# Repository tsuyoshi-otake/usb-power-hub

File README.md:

# USB Power-Control Hub

A 2-channel switched USB-C hub that measures each downstream port's current from
0.1 µA to 1 A, so a device under test can be power-profiled and power-cycled from
the host PC over a plain COM port.

*A rendered picture of the design files, not a photograph: nothing is printed or assembled
yet. [What it looks like](#what-it-looks-like) explains each face.*

> **Status (2026-11-21): the main board is ordered and in production. Nothing is built or
> measured, and there is no firmware.**
>
> - **Main board, Rev0.7 r01: `ORDERED`.** The user ordered it from JLCPCB and paid for it on
>   2026-11-20 (5 boards, 2 of them assembled) and had the production file confirmed on
>   2026-11-21. Its files are `manufacturing/releases/rev0.7/r01/` and are never overwritten.
>   It went out with gates open: JLCDFM never ran on Rev0.7, the stackup was not named on the
>   order, and the open issues of `CLAUDE.md` Section 11 stand (`RELEASE_MANIFEST.md` there,
>   *Open gates*). Its solder mask is green: JLCPCB takes only green on an Economic 4-layer
>   order.
> - **Enclosure, Rev0.5: drawn, not printed.** A printed tray, frame and cover with a PCB lid
>   let into the frame (`design/mechanical/`). No cable has been tried in an opening.
> - **Lid PCB, Rev0.2: drawn, not ordered.** JLCPCB has not seen its files.
> - **Firmware: does not exist.** The PC software (`host/profiler/`) runs against its demo
>   device.
> - **Every other release** (`manufacturing/releases/rev0.4/` to `rev0.6/`) stays `WIP` and
>   is not orderable. No further order is placed without the user's approval.

## What it is meant to do

- **Two USB-C inputs:**
  - `HOST` (J1) carries data and logic power from the PC.
  - `5V IN` (J4) is a power-only 5 V input that feeds the ports. Its USB-C current
    advertisement is read and enforced.
  - There is no USB-PD and no port regulator: the port voltage is J4's minus up to 0.40 V
    at 1 A (0.48 V when the other port also draws 1 A; the input fuse is shared).
- **Downstream:** two USB-C receptacles (`OUT A`, `OUT B`), each switched on and off
  independently by firmware. They are OFF at power-up and after any reset (REQ-PORT-01),
  and offer Default USB power (500 mA), with a hardware over-current trip at 1.16 A. Each
  port's D+ and D− are also tapped through 1 kΩ to four RP2040 GPIO for a Low-Speed and
  Full-Speed capture of the device under test (D38, issue #10); firmware for it does not exist.
- **Measurement:** per port, a 3-range shunt ladder (510 Ω / 10 Ω / 0.1 Ω) with hardware
  up-ranging, discrete current-mirror amplifiers, and two 12-bit MCP3208 ADCs (one per
  port, sampled together), at 14.0 kSPS per channel. Accuracy target: ±(1 % + 3 LSB of the range).
- **Control:** an RP2040 with its own flash and crystal, machine-placed (D29), behind a CH335F hub, also machine-placed (D31), enumerating as a driverless CDC-ACM COM
  port. Commands such as `PORT A ON`, `PORT B CYCLE 2000` and `STREAM ON` are listed in
  `requirements/product.md` Section 4.1.
- **Board:** 100 × 72 mm, 4 layers, 1.6 mm FR-4 (D24), leaded HASL (D30). The earlier 85 × 35 mm
  cannot hold the Rev0.4 parts. JLCPCB's instant quote on 2026-11-03 (4 layers, 5 pcs,
  default options, leaded HASL) was $8.00 at 85 × 35, 100 × 72 and 100 × 100 mm; ENIG would
  add $16.90 and $17.40 at the two sizes. Recheck the live quote before ordering. The stackup is
  JLC04161H-7628, named on the order, without impedance control for the prototype (D27).
  - JLCPCB machine-places the small parts, the RP2040, the CH335F and the four USB-C
    receptacles, all JLCPCB **Basic** except those three parts (Extended, the user's three
    exceptions, D29, D31 and D37).
  - You hand-solder the large parts, all bought from **Akizuki**: two DIP16 ADCs, the 12 V
    module, two shunts per port and the input fuse.
  - This is the sourcing rule D13. D22 excludes Preferred Extended parts too, so the
    D+/D− lines of J1–J3 have no ESD protection (`requirements/product.md` §9).

## What it looks like

The unit is 104.8 × 76.8 × 27.7 mm, everything matte black (Enclosure E2, Lid K7). The
pictures are rendered from the generated design files: the enclosure's STL files and the lid's
KiCad board. They are not photographs and they prove nothing. Nothing is printed, the lid PCB
is not ordered, and the screws, the receptacles and the lit LEDs are drawn by the render
script.

| Front | Back |
|---|---|
|  |  |
| `OUT A` (left) and `OUT B` (right), the two switched and measured ports, 65 mm apart. Each opening has a 15.0 × 8.0 mm pocket for the plug's overmould (E6). The line along the wall is the seam between the tray below and the frame above. | `HOST` (data and logic power from the PC) and `5V IN` (the power-only input that feeds the ports). The flat piece between them is the printed cover (E11) of the opening for the SWD spring-pin clamp (J5, D40): it is drawn out with a fingernail before the clamp goes on. |

The top is a PCB, not a printed part (Lid Rev0.2: bare 2-layer, 1.6 mm, matte black mask,
white legend, no component and no net).

1. **It lies inside the case.** The frame's wall goes on up round the lid, as high as the
   lid is thick, so the lid's edge is not seen and its top face is flush with the wall's
   (E12; 0.4 mm between lid and wall).
2. **Four M2 screws** hold it on the frame's posts; four more from below clamp the main board
   between tray and frame (E4, heat-set inserts).
3. **A label and an arrow for each port:** `HOST`, `5V IN`, `OUT A`, `OUT B`.
4. **A button and a window beside each output.** The button is a loose printed plunger over
   the port's switch on the main board. The window is bare FR-4, with no copper and no mask,
   over the port's two LEDs (green: port on, red: port fault), so no light pipe is needed (E8).
5. **`BOOT` is a pinhole** for a paperclip to SW3, which starts the RP2040's USB bootloader
   without opening the case (REQ-BOOT-02).

What is not known before a print (the lid's fit in its pocket, how the support under the
lid's seat comes off, the cover's click, a real cable in an opening) is listed in
`design/mechanical/ENCLOSURE_Rev0.5.md` §10. To draw the pictures again, with Blender 5.x and
KiCad 9.0 (about 1 min on a GPU):

```sh
"<Blender>/blender.exe" -b --python design/mechanical/scripts/render_unit.py -- --kicad-cli "<KiCad 9.0>/bin/kicad-cli.exe"
```

## Documents

Read in this order:

| File | What it holds |
|---|---|
| `CLAUDE.md` | Engineering policy, release discipline, and the open-issue list (Section 11). Every unstruck open issue blocks manufacturing. |
| `requirements/product.md` | What the product must do — the authority. REQ-* IDs, each marked Settled / Delegated / Proposed / Open / Withdrawn. Includes the control protocol. |
| `requirements/verification.md` | How each requirement is proven (V-* IDs: method, pass criterion, limits). |
| `design/circuit/CIRCUIT_DESIGN_Rev0.7.md` | The schematic as a document: topology, nets, designators, calculations, decisions (§10), and what was given up to meet the sourcing rule (§7.4). Rev0.1–Rev0.4 are in Git history (Rev0.4 at commit `5a697aa`). |
| `requirements/parts.md` | Candidate parts: JLCPCB Basic rows (LCSC number, assembly stock, class, date) and Akizuki rows (code, stock, price, date). Candidates only — none is confirmed. |
| `design/ecad/` | The KiCad 9 project (D32): `source/` holds the project, the source of truth until the EasyEDA import; `scripts/` holds its generators and checks; `libraries/` holds the project's symbols and footprints and the parts register they are checked against (its README). So far: stackup, outline, rules, net classes, the libraries, the schematic, written from `design/circuit/CIRCUIT_DESIGN_Rev0.7_netlist.md` (the capture list: every part, pin and net) and checked against it, the placement and silkscreen, written from `design/ecad/PLACEMENT_Rev0.7.md` (where every part and label sits, and why), and the routing, from `design/ecad/ROUTING_Rev0.7.md`; `make_outputs.py` writes the candidate manufacturing set from the board. `design/ecad/README.md` gives the order to run the generators in. |
| `design/experiments/oi-23-placement/` | The OI-23 placement study: why 85 × 35 mm cannot work, and the checked 100 × 72 mm block placement. A trial, not design data. |
| `design/experiments/stackup-impedance/` | The stackup study behind D27: JLCPCB's 4-layer stackups, the 90 Ω USB pair width on each, and a model checked against JLCPCB's single-ended calculator. A non-authoritative study, not design data. |
| `design/experiments/cost-estimate/` | Prototype cost estimate, dated 2026-11-03, re-run 2026-11-04 for D29, D30, D31 and D33, with Rev0.4's real quote (2026-11-12), the Rev0.5 delta for D37 and D38 and Rev0.5's quote (2026-11-13): 5 bare PCBs with 2 assembled by JLCPCB, plus the Akizuki parts. An estimate, not a quote. |
| `design/experiments/usb-symmetry-c2/` | Trial C2 (issue #12): the four USB-C receptacles and the two buttons mirrored about the board's centre line, at placement level and, without a patch, at routing level. The parts fit and `check_pcb.py` passes on a footprint-only board; one router run left 15 connections open, against 16 on the board at the same stage. A trial, not design data. D39 then took its placement into the board as Rev0.6 (issue #13); the board's routing is its own (`design/ecad/ROUTING_Rev0.7.md`), not the trial's. |
| `design/mechanical/` | The enclosure (issue #11; Rev0.5 for the Rev0.7 board, issue #14), a first design on paper: `ENCLOSURE_Rev0.5.md` (a printed tray and frame with a PCB lid let into the frame, 104.8 × 76.8 × 27.7 mm; its decisions E1–E12, the opening for the SWD clamp, its printed cover and the wall round the lid among them, and what is not verified), the board's mechanical interface exported from the KiCad board, the STL files, eleven pictures of the build, four realistic renders of the assembled unit (`render_unit.py`, for looking at), and the scripts that generate and check them (its README). Nothing is printed and no cable has been tried. The lid PCB is drawn as its own KiCad board (`LID_Rev0.2.md`, `lid/`: bare 2-layer, the main board's outline, the legend on its top); it is not ordered. |
| `host/profiler/` | The PC software (issue #9): a native Win32 current profiler in Rust that plots both channels, switches the ports and exports CSV. Runs against its demo device until firmware exists (its README). |
| `mockup/` | three.js appearance model of an earlier 60 × 24 mm, 6-layer concept. Reference only; superseded by the board-size decisions D10 and D24 (100 × 72 mm). |

Decisions are D-numbers in the circuit document's §10. Its "By" column says whether the
user made each one, whether it came from the Rev0.1 design, or whether Claude made it
under the user's 2026-11-03 delegation ("Claude (delegated)"). The user may revert a
delegated decision. Rev0.2's proposals (P-numbers) are resolved in §14.

## Re-checking part stock

Stock in `requirements/parts.md` is a dated snapshot. To re-query the JLCPCB
assembly-parts pool (Python 3, standard library only, no install step; checked with 3.13):

```sh
python tools/jlc_stock.py C7433 OP07CDR
python tools/jlc_stock.py --all OP07      # list every hit, for finding candidates
```

The full command for every listed part is at the top of `requirements/parts.md`.
Exit status: 0 = every query matched exactly, 1 = some query did not, 2 = the API
failed. The tool's docstring lists what it cannot see — electrical suitability,
order-time stock, footprints, price, and lifecycle. Akizuki stock has no tool: read the
product page (codes in `requirements/parts.md`) at order time.

## Viewing the mockup

The mockup loads three.js from unpkg, so it needs a network connection and an
HTTP server (ES modules do not load from `file://`):

```sh
python -m http.server 8000 --directory mockup
# then open http://localhost:8000/usb-power-hub-board.html
```

## Building and programming

Not possible yet: the first boards are in production at JLCPCB (Rev0.7 r01, ordered on
2026-11-20; `manufacturing/releases/rev0.7/r01/`, state `ORDERED`), and firmware does not
exist. What follows is how the design came to that order; the gates it names are Rev0.5's and
Rev0.6's. The board is captured and laid out in KiCad 9.0.8 until the design is
complete, then imported into EasyEDA (decision D32, issue #6). Every part has a symbol and
a footprint, the RP2040's, the CH335F's and the USB-C receptacle's lands drawn from their
datasheets or maker's drawing (G20, G21, D37). The schematic is captured (issue #6 P2,
D34) and includes J1's soft start (D35, issue #7) and the four data-line taps (D38, issue
#10). The parts are placed (P3) and routed (P4, under D36's L3/L4 rule): DRC reports 0
violations and 0 unconnected items, and `check_routing.py` rule 9 keeps the L2 plane whole
under U1 and U6. Rev0.6 moved 31 parts with the connectors (D39) and carries Rev0.5's routing
where it still stands (`design/ecad/scripts/carry.py`); the rest is a new router session and
a new patch. Rev0.7 changes J5's land (D40) and carries Rev0.6's routing the same way, with the
tracks at J5 drawn in the routing document. The silkscreen labels are placed, and a candidate manufacturing set (P5:
Gerber, drill, JLCPCB BOM and CPL, schematic PDF, renders, a `WIP` manifest) is generated
into `manufacturing/working/rev0.7/`, which Git does not track and nobody may order from;
`manufacturing/releases/rev0.5/r02/` holds Rev0.5's files as a release candidate (state
`WIP`, nothing ordered; r01 beside it is superseded). The JLCPCB gate ran on 2026-11-13
(JLCDFM, part mapping, the placement preview of the receptacle, a quote of $51.94 without
shipping; `JLCPCB_REVIEW.md`) and found two defects in r01, both fixed in r02: the receptacle's
JLCPCB model sat 1.375 mm off the CPL point, and eight vias stood 0.046 mm from its plated
slots. The decisions it leaves are the user's (the 0.60 mm slot width, impedance control,
shipping, approval); then comes the EasyEDA import (P6). The front-end checks are made on the first assembled board, not on a
bench beforehand (decision D28). Firmware does not exist.

The KiCad project, its libraries, its schematic and its board are generated, not hand-edited. With KiCad
9.0's own Python, from the repository root:

```sh
"<KiCad 9.0>/bin/python.exe" -I -B design/ecad/scripts/make_project.py           # writes and checks design/ecad/source
"<KiCad 9.0>/bin/python.exe" -I -B design/ecad/scripts/test_make_project.py      # the check's negative tests
"<KiCad 9.0>/bin/python.exe" -I -B design/ecad/scripts/make_libraries.py         # writes and checks design/ecad/libraries
"<KiCad 9.0>/bin/python.exe" -I -B design/ecad/scripts/test_check_libraries.py   # its negative tests
"<KiCad 9.0>/bin/python.exe" -I -B design/ecad/scripts/make_schematic.py         # writes the schematic, runs ERC and check_schematic.py
"<KiCad 9.0>/bin/python.exe" -I -B design/ecad/scripts/test_check_schematic.py   # its negative tests
"<KiCad 9.0>/bin/python.exe" -I -B design/ecad/scripts/autoroute.py --java <java.exe> --jar <freerouting-2.5.0.jar>  # only when its input changed
"<KiCad 9.0>/bin/python.exe" -I -B design/ecad/scripts/make_pcb.py               # places, routes and labels; runs check_pcb.py, check_routing.py, check_silk.py
"<KiCad 9.0>/bin/python.exe" -I -B design/ecad/scripts/test_check_pcb.py         # its negative tests
"<KiCad 9.0>/bin/python.exe" -I -B design/ecad/scripts/test_check_routing.py
"<KiCad 9.0>/bin/python.exe" -I -B design/ecad/scripts/test_check_silk.py
"<KiCad 9.0>/bin/python.exe" -I -B design/ecad/scripts/make_outputs.py           # writes manufacturing/working/rev0.7, runs check_outputs.py
"<KiCad 9.0>/bin/python.exe" -I -B design/ecad/scripts/test_check_outputs.py     # its negative tests
```

`make_project.py` writes a bare board, so `make_pcb.py` runs after it. `autoroute.py` needs
Freerouting 2.5.0 and a Java runtime, which are not in the repository
(`design/ecad/README.md`). A release candidate is also read against the board by two scripts that
share nothing with the generators, `independent_check_sets.py` and
`independent_check_positions.py` (`design/ecad/README.md`, *Independent check of a candidate set*).

## Repository

- Git since 2026-11-03. Commit `4dd10fb` is the design exactly as it was paused
  on 2026-08-16; later commits are the 2026-11-03 revision.
- **Remote:** `origin` is the GitHub repository `tsuyoshi-otake/usb-power-hub`, private from
  2026-11-03 and public since 2026-11-20 by the user's decision, under the MIT licence
  (`LICENSE`). No account data, credential or address goes into it (`CLAUDE.md` Section 2).
- Commit messages are English and describe the change in detail.

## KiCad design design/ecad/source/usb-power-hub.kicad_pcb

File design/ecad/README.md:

# KiCad project (Rev0.7, issues #6, #8, #10, #13, #14)

> **WIP — MANUFACTURING PROHIBITED.** Rev0.7 is captured, placed, routed and labelled in
> KiCad 9.0.8 until the design is complete, then imported into EasyEDA (D32). Its candidate
> manufacturing set (step 7) is a `WIP` set: nothing here is orderable.

Everything under `source/` and `libraries/` is generated by the scripts in `scripts/` from
documents in the repository. Change the document, then re-run the generator. A board or
schematic saved from the KiCad GUI is overwritten by the next run; open the project to look,
not to edit.

| Path | Holds |
|---|---|
| `source/` | The KiCad project: `usb-power-hub.kicad_pro` (rules, net classes), `usb-power-hub.kicad_dru` (JLCPCB's hole figures for vias and PTH pads as custom DRC rules, issue #8), the root sheet and six sub-sheets, `usb-power-hub.kicad_pcb` (stackup, outline, placed footprints). |
| `libraries/` | The project symbols and footprints and `library.json`, the datasheet facts they are checked against (its README). |
| `PLACEMENT_Rev0.7.md` | Where every part sits on the board, and why (P3), and its silkscreen labels: text, position, size, stroke and leader (P5). |
| `ROUTING_Rev0.7.md` | The plane, the hand-drawn tracks (USB pairs, Kelvin taps, power trunks), the zones, the router's classes, keepouts, layer preferences and costs, the patch drawn after the router, and why (P4). |
| `routing/` | `carried.json`, the tracks and vias of Rev0.5's routing that still stand on this board (written by `carry.py`); the router's session `usb-power-hub.ses` and `autoroute.json`, which records the router input, the jar, the Java runtime and the arguments that produced it. |
| `scripts/` | The generators, their checkers and the checkers' negative tests; the two independent checks of a candidate set. |

## Pipeline

Run with KiCad 9.0's own Python, which carries `pcbnew`, from the repository root, in this
order. Each generator runs its checker when it has written its files; exit status 0 means
written and checked.

| Step | Script | Reads | Writes | Checked by | Negative tests |
|---|---|---|---|---|---|
| 1 | `make_project.py` | `design/experiments/stackup-impedance/stackups.json` | `.kicad_pro`, `.kicad_dru`, a bare `.kicad_pcb` | `make_project.py --check` | `test_make_project.py` |
| 2 | `make_libraries.py` | `libraries/library.json` | `libraries/usb-power-hub.kicad_sym`, `usb-power-hub.pretty/` | `check_libraries.py` | `test_check_libraries.py` |
| 3 | `make_schematic.py` | `design/circuit/CIRCUIT_DESIGN_Rev0.7_netlist.md` (the capture list), the symbols | the seven `.kicad_sch` | ERC, `check_schematic.py` | `test_check_schematic.py` |
| 4 | `carry.py` | the step-6 inputs up to the GND fanout; the previous revision's carried record, session and patch table (Rev0.6's), read from Git history at the commit the carry table of `ROUTING_Rev0.7.md` names | `routing/carried.json` | `carry.py --check`; `make_pcb.py`, which refuses a record made for another board or from other sources | `test_carry.py` |
| 5 | `autoroute.py` | what `make_pcb.py --dsn` writes from the step-6 inputs, the carried record included | `routing/usb-power-hub.ses`, `routing/autoroute.json` | `make_pcb.py`, which refuses a session made from other input | — |
| 6 | `make_pcb.py` | the schematic's exported netlist, `PLACEMENT_Rev0.7.md`, `ROUTING_Rev0.7.md`, the carried record, the session, the footprints | `.kicad_pcb` | `make_project.py --check`, `check_pcb.py`, `check_routing.py` (each with DRC), `check_silk.py` | `test_check_pcb.py`, `test_check_routing.py`, `test_check_silk.py` |
| 7 | `make_outputs.py` | the project in `source/`, `design/ecad/jlcpcb_model_frame.json` | `manufacturing/working/rev0.7/`: Gerber and drill zip, JLCPCB BOM and CPL, hand-solder list, schematic and assembly PDFs, two renders, ERC and DRC reports, `RELEASE_MANIFEST.md` (state `WIP`), `SHA256SUMS.txt` | `check_outputs.py` | `test_check_outputs.py` |

```sh
"<KiCad 9.0>/bin/python.exe" -I -B design/ecad/scripts/make_project.py
"<KiCad 9.0>/bin/python.exe" -I -B design/ecad/scripts/make_libraries.py
"<KiCad 9.0>/bin/python.exe" -I -B design/ecad/scripts/make_schematic.py
"<KiCad 9.0>/bin/python.exe" -I -B design/ecad/scripts/carry.py
"<KiCad 9.0>/bin/python.exe" -I -B design/ecad/scripts/autoroute.py --java <java.exe> --jar <freerouting-2.5.0.jar> --passes 8
"<KiCad 9.0>/bin/python.exe" -I -B design/ecad/scripts/make_pcb.py
"<KiCad 9.0>/bin/python.exe" -I -B design/ecad/scripts/make_outputs.py
```

Step 4 needs the repository's Git history: it reads Rev0.6's carried record, session and patch table at the
commit the carry table names, and takes about 8 s on this machine. It is needed only when its
inputs change: `make_pcb.py` stops and asks for it when the record no longer matches the carry
table or the board before the carry.

Step 5 needs Freerouting 2.5.0 and a Java runtime, which are not in the repository; the
script refuses any jar or runtime other than the pinned ones (their SHA-256 is in the
script). It is needed only when its input changes: `make_pcb.py` stops and asks for it when
the session no longer matches the board it would route. The committed session took about
5 min on this machine (8 passes, single-threaded; `ROUTING_Rev0.7.md`, *Router*, says why more
passes change nothing while the carried copper is fixed). A new record or a new session also
needs a new patch table (`ROUTING_Rev0.7.md`, *After the router*).

`make_project.py` writes a bare board, so `make_pcb.py` runs after it; until then
`check_pcb.py` fails, because the board holds no footprints. A re-run of any generator but
`make_pcb.py` writes the same bytes: UUIDs are derived, and `make_pcb.py` seeds pcbnew's UUID
generator, which decides the order footprints are saved in.

`make_pcb.py` writes the same bytes except for the pours' fill: KiCad's zone filler is not
deterministic. Measured on the Rev0.5 board (commit `866ef44`): in 32 runs on 2026-11-13 (a
scratch copy of `design/`, `--no-check`), 3 left out two 0.11 mm² islands of the B.Cu GND pour
that touched pad J3.S1 where it then stood (x 96.73-97.23 and 105.37-105.87, y 117.0-117.3 mm)
and 29 kept them; the board file then differed by those two filled polygons and the Gerber's
`B_Cu` member with it. Nothing else differed, and both boards passed every check. The Rev0.6 board
has not been run that way. The tracked `source/usb-power-hub.kicad_pcb` is therefore the source of
truth, and a release is made from it. Do not regenerate it to compare, and read a changed board
hash after a re-run as this, not as a changed design, before looking for another cause. Step 7 is
deterministic given the board.

Step 7 writes a candidate, not a release. `manufacturing/working/` is not tracked
(`.gitignore`; CLAUDE.md §2: disposable, never orderable), so the set is regenerated rather
than checked out: the same sources, the board included, give the same bytes, because creation
dates are fixed to 1980-01-01 and paths made relative. Its manifest records the SHA-256 of every source file
instead of a Git commit, and `check_outputs.py` fails a set older than its sources. A
release is copied to `manufacturing/releases/<rev>/<rNN>/` and tracked there (CLAUDE.md §2).

The CPL's angles are KiCad's plus a per-LCSC rotation, and its positions KiCad's plus a per-LCSC
shift; both are in `jlcpcb_model_frame.json` (until 2026-11-13 `jlcpcb_model_rotation.json`,
rotations only), because JLCPCB applies a CPL point and angle to its own model of the part
(easy-stick 14.18). `make_outputs.py` reads it and `check_outputs.py` fails an entry no BOM line
uses. Gerber and drill files are written with the auxiliary origin at the board's lower-left
corner, the CPL's origin. A new entry or a new part class is confirmed only in JLCPCB's
placement preview, after the corrected CPL is uploaded; the first review is
`manufacturing/releases/rev0.4/r01/JLCPCB_REVIEW.md`, and its candidate release is the first one
under `manufacturing/releases/` (state `WIP`, not approved). Rev0.4's `r02` beside it is the
same copper with every via drilled at 0.30 mm, JLCPCB's standard via class (issue #8); its
`JLCPCB_REVIEW.md` records only what changed. Rev0.5's gate ran on 2026-11-13 on
`manufacturing/releases/rev0.5/r01/` and found two defects: the receptacle C2765186's (D37)
model sat 1.375 mm off the CPL point, hence the `shift`, and eight vias stood 0.046 mm from the
receptacles' plated slots, hence rule 10 of `check_routing.py` and the *Slot vias* stage of
Rev0.5's routing patch (since Rev0.6 the GND fanout draws those stubs itself).
`manufacturing/releases/rev0.5/r02/` fixes both (state `WIP`, not approved); its
`JLCPCB_REVIEW.md` is the gate's record, and r01's beside it a short one.

The negative tests corrupt copies of the files in a temporary directory and expect the
checker to name each fault; they never write to `source/`, `libraries/` or `manufacturing/`.

## Independent check of a candidate set

`check_outputs.py` reads the board with `pcbnew`, as `make_outputs.py` does.
Two more scripts read the files JLCPCB receives against the board's text, by regular
expressions. They import nothing from this directory and no KiCad module (KiCad's Python serves
as a plain interpreter), and they are not a pipeline step: run them on a release candidate, after
`sha256sum -c` (CLAUDE.md §12, the manifest's gate "Independent check of the set").

| Script | Reads | Checks | Corruptions |
|---|---|---|---|
| `independent_check_sets.py` | the Gerber zip, the CPL, the BOM, the hand-solder list, the silkscreen table of `PLACEMENT_Rev0.7.md`, the board | 30 with three fiducials: no Bottom paste, the outline, each fiducial in copper and mask, the CPL's side and bounds, the hand-solder list apart from BOM and CPL, BOM against CPL, the 16 test pads of REQ-MFG-04 | 8 |
| `independent_check_positions.py` | the Gerber zip, the CPL, the BOM, the hand-solder list, the board, `jlcpcb_model_frame.json`, the previous release's Gerber zip and CPL | 13: the parts and their codes in the three lists, every CPL point and rotation, every Top paste flash, every hit of the two drill files | 16, three of them the previous release's files in the place of this set's |

```sh
R=manufacturing/working/rev0.7/UsbPowerHub_Main_Rev0.7
P=manufacturing/releases/rev0.5/r02/UsbPowerHub_Main_Rev0.5
"<KiCad 9.0>/bin/python.exe" -I -B design/ecad/scripts/independent_check_sets.py \
    ${R}_Gerber.zip ${R}_CPL_JLCPCB.csv ${R}_BOM_JLCPCB.csv ${R}_HandSolder.csv \
    design/ecad/PLACEMENT_Rev0.7.md design/ecad/source/usb-power-hub.kicad_pcb
"<KiCad 9.0>/bin/python.exe" -I -B design/ecad/scripts/independent_check_positions.py \
    ${R}_Gerber.zip ${R}_CPL_JLCPCB.csv ${R}_BOM_JLCPCB.csv ${R}_HandSolder.csv \
    design/ecad/source/usb-power-hub.kicad_pcb design/ecad/jlcpcb_model_frame.json \
    ${P}_Gerber.zip ${P}_CPL_JLCPCB.csv
```

Each prints `PASS` or `FAIL` per check, then `CAUGHT` or `MISSED` per corruption, and exits 0
only when every check passed and every corruption was caught (1 otherwise, 2 for a wrong number of
arguments). The corruptions are made on in-memory copies in the same run, so a result always comes
with the proof that the checker can fail; neither script writes a file, and neither has a `test_`
script. On Rev0.6 r01 (2026-11-19): 30 checks, 0 failed, 8 corruptions, 0 missed, and 13 checks,
0 failed, 16 corruptions, 0 missed, in 0.3 s and 0.6 s on this machine. Rev0.6 r02 and Rev0.7
r01 give the same figures. The second script's last argument must be a set of another PCB revision: r01 beside r02
shares its CPL, paste and drill files, so three of the corruptions made from it change nothing and
are reported `MISSED`.

The first script reads no position but the fiducials': with Rev0.5 r02's CPL beside the Rev0.6
board it passes all 30 checks, and the second then fails on 28 CPL rows. The second is therefore
the one that tells a layout revision's set from the one before, and its last two arguments must
name a release whose parts and holes stand elsewhere: with a release given as its own predecessor
the three substitutions are no corruption, they are reported `MISSED`, and the exit status is 1.

Both take the board as right. They show that the BOM, the CPL, the hand-solder list, the Top
paste Gerber and the two drill files are this board's; they read no copper, mask or silkscreen
layer and no pad shape (each docstring's "What it CANNOT see"). Until 2026-11-19 they were scratch
scripts outside the repository, `c2_check.py` (issues #6 and #8) and `c2_ext_rev06.py` (issue #13),
and records written before that day name them so.

## Where a change starts

| Change | Edit | Then run |
|---|---|---|
| A part, pin or net | the capture list | steps 3 to 7 |
| A part's position or rotation | `PLACEMENT_Rev0.7.md` | steps 4 to 7 |
| A silkscreen label | `PLACEMENT_Rev0.7.md`, *Silkscreen* | steps 6 and 7 (labels are not router input) |
| A hand-drawn track, a zone, a router class or keepout | `ROUTING_Rev0.7.md` | steps 4 to 7 |
| A row of the carry table (*Carried from Rev0.6*) | `ROUTING_Rev0.7.md` | steps 4 to 7 |
| A row of the patch table (*After the router*) | `ROUTING_Rev0.7.md` | steps 6 and 7 (the record and the session stay: the patch is not router input) |
| A part's JLCPCB model rotation or shift | `jlcpcb_model_frame.json` | step 7, then the JLCPCB placement preview |
| A symbol or footprint | `libraries/library.json`, `make_libraries.py` | steps 2 to 7 |
| Rules, net classes, stackup, outline | `make_project.py` | step 1, then 4 to 7 |

## What the checks cannot see

Each checker's docstring ends with a "What it CANNOT see" list (CLAUDE.md §8). In short: the
checkers compare the KiCad files with the documents, not the documents with the physics.
Whether the circuit is right is the circuit document's and its `_calc.py`'s; whether the
routing is good beyond the rules `check_routing.py` lists is a review's (its rule 9 reads the 2-D
copper fill of L2, as voids and exposed-pad webs, and not the return currents: a void shorter
than 3.0 mm still lengthens a return path, and the router, which knows no antipad, sees none of
it); heights, the plug overmold and the enclosure are V-MECH-01's; whether JLCPCB reads the set as
meant (DFM, part mapping, the CPL's origins and angles in its placement preview) is the JLCPCB
gate's (CLAUDE.md §8, easy-stick 14.18).

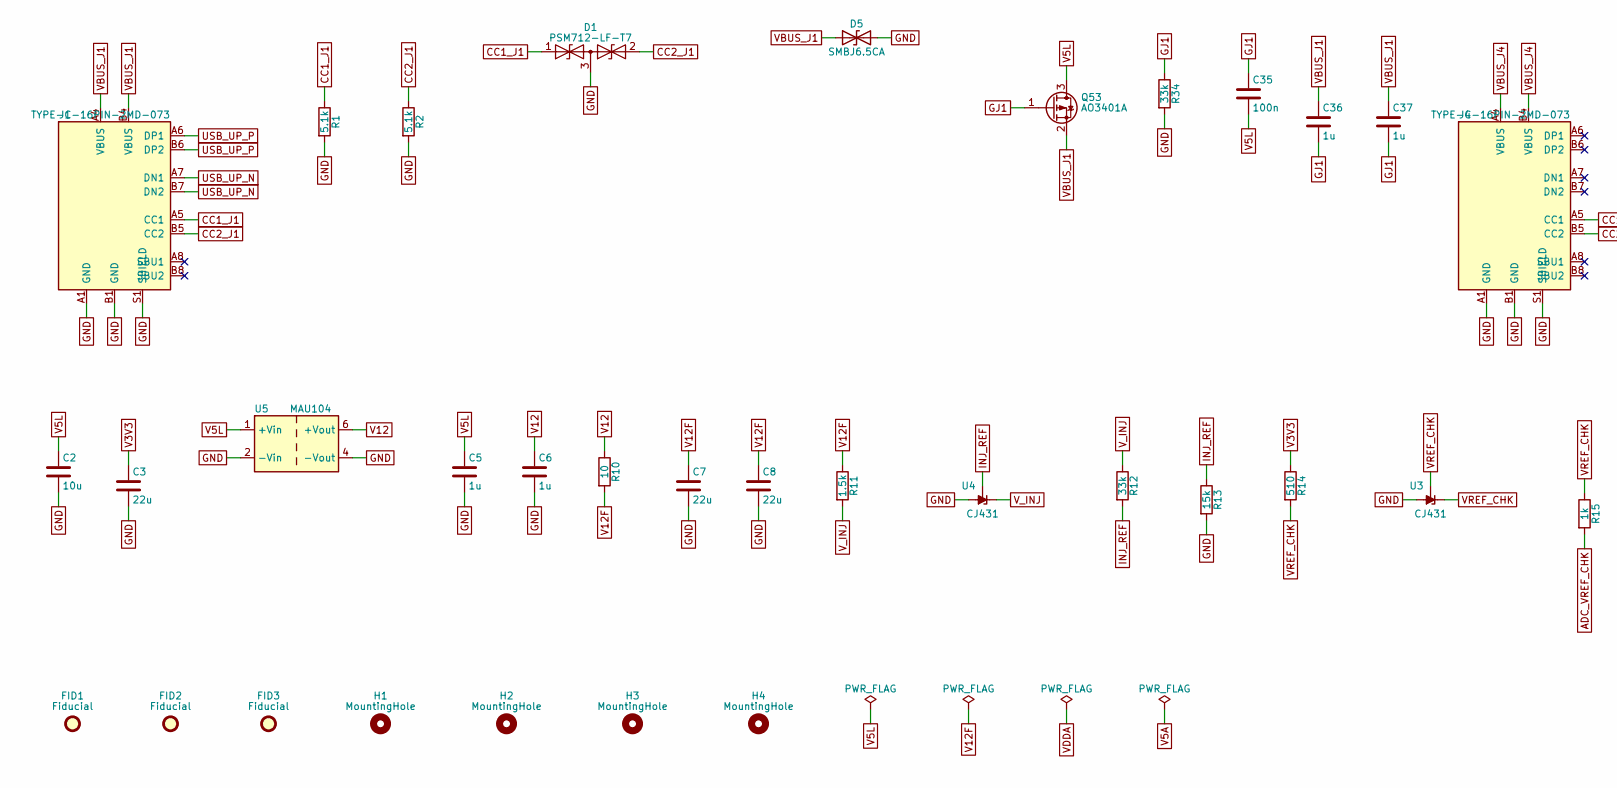
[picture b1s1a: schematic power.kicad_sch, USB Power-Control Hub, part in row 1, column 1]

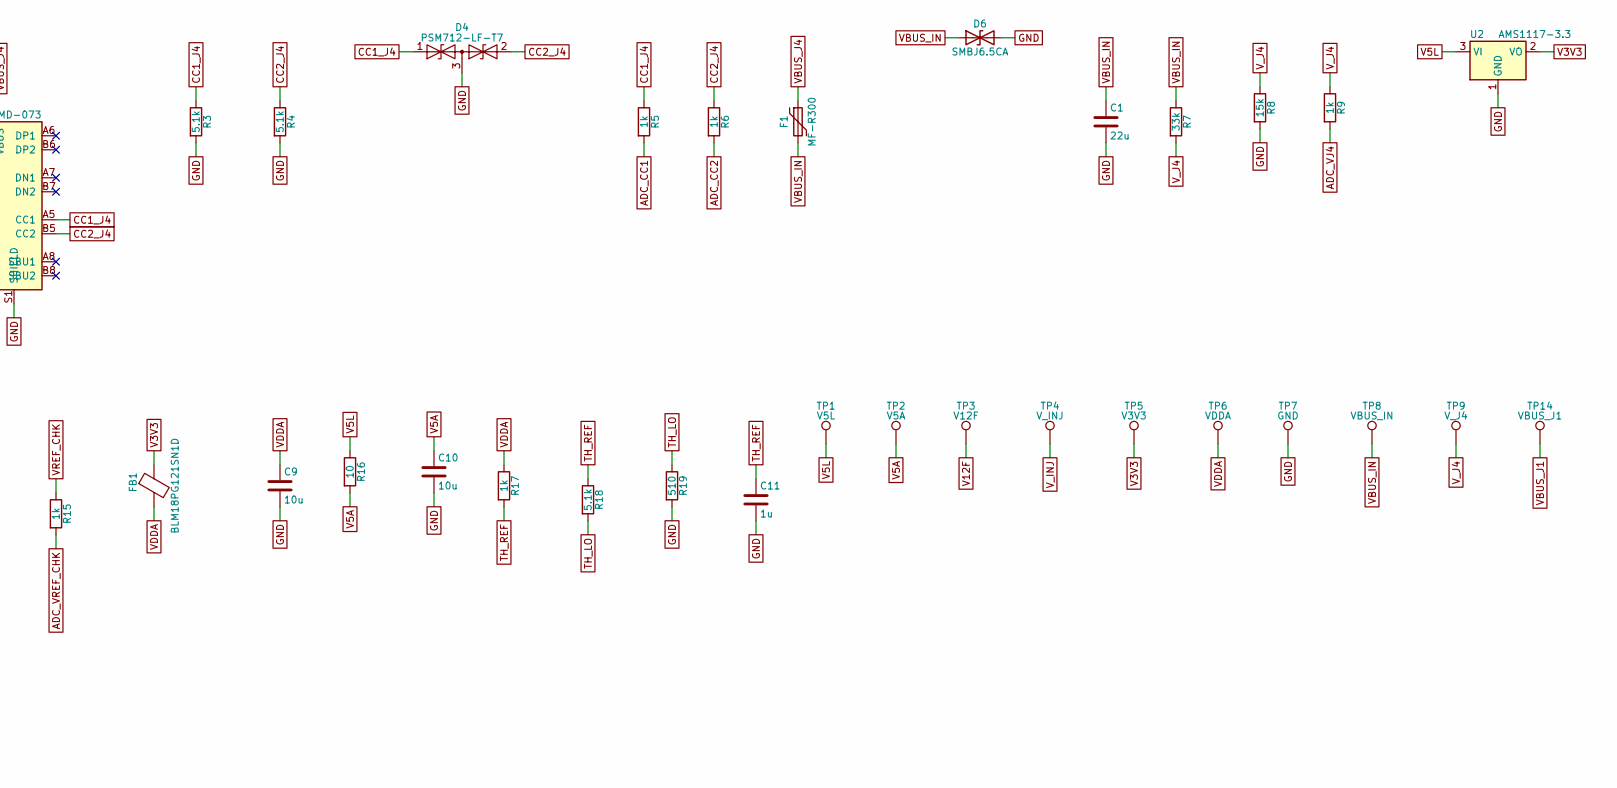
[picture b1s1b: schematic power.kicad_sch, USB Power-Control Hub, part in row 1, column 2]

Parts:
C1, C3, C7, C8: 22u; C_0805_2012Metric; MPN CL21A226MAQNNNE; LCSC C45783
C2, C9, C10: 10u; C_0805_2012Metric; MPN CL21A106KAYNNNE; LCSC C15850
C5, C6, C11, C36, C37: 1u; C_0402_1005Metric; MPN CL05A105KA5NQNC; LCSC C52923
C35: 100n; C_0402_1005Metric; MPN CL05B104KB54PNC; LCSC C307331
D1, D4: PSM712-LF-T7; SOT-23; MPN PSM712-LF-T7; LCSC C32677
D5, D6: SMBJ6.5CA; D_SMB; MPN SMBJ6.5CA; LCSC C7420377
F1: MF-R300; Fuse_Bourns_MF-R300_Style2_P5.10mm; MPN MF-R300
FB1: BLM18PG121SN1D; L_0603_1608Metric; MPN BLM18PG121SN1D; LCSC C14709
FID1, FID2, FID3: Fiducial; Fiducial_1mm_Mask2mm
H1, H2, H3, H4: MountingHole; MountingHole_2.2mm_M2_ISO7380
J1, J4: TYPE-C-16PIN-2MD-073; USB_C_Receptacle_SHOUHAN_TYPE-C-16PIN-2MD-073; MPN TYPE-C 16PIN 2MD(073); LCSC C2765186
Q53: AO3401A; SOT-23; MPN AO3401A; LCSC C15127
R1, R2, R3, R4, R18: 5.1k; R_0402_1005Metric; MPN 0402WGF5101TCE; LCSC C25905
R5, R6, R9, R15, R17: 1k; R_0402_1005Metric; MPN 0402WGF1001TCE; LCSC C11702
R7, R12, R34: 33k; R_0402_1005Metric; MPN 0402WGF3302TCE; LCSC C25779
R8, R13: 15k; R_0402_1005Metric; MPN 0402WGF1502TCE; LCSC C25756
R10, R16: 10; R_0402_1005Metric; MPN 0402WGF100JTCE; LCSC C25077
R11: 1.5k; R_0402_1005Metric; MPN 0402WGF1501TCE; LCSC C25867
R14, R19: 510; R_0805_2012Metric; MPN 0805W8F5100T5E; LCSC C17734
TP1: V5L; TestPoint_Pad_D1.0mm
TP2: V5A; TestPoint_Pad_D1.0mm
TP3: V12F; TestPoint_Pad_D1.0mm
TP4: V_INJ; TestPoint_Pad_D1.0mm
TP5: V3V3; TestPoint_Pad_D1.0mm
TP6: VDDA; TestPoint_Pad_D1.0mm
TP7: GND; TestPoint_Pad_D1.0mm
TP8: VBUS_IN; TestPoint_Pad_D1.0mm
TP9: V_J4; TestPoint_Pad_D1.0mm
TP14: VBUS_J1; TestPoint_Pad_D1.0mm
U2: AMS1117-3.3; SOT-223-3_TabPin2; MPN AMS1117-3.3; LCSC C6186
U3, U4: CJ431; SOT-23; MPN CJ431; LCSC C3113
U5: MAU104; Converter_DCDC_Minmax_MAU104_SIP; MPN MAU104

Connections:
ADC_CC1: R5.2; also elsewhere on the board
ADC_CC2: R6.2; also elsewhere on the board
ADC_VJ4: R9.2; also elsewhere on the board
ADC_VREF_CHK: R15.2; also elsewhere on the board
CC1_J1: D1.1 (A1), J1.A5 (CC1), R1.1
CC1_J4: D4.1 (A1), J4.A5 (CC1), R3.1, R5.1
CC2_J1: D1.2 (A2), J1.B5 (CC2), R2.1
CC2_J4: D4.2 (A2), J4.B5 (CC2), R4.1, R6.1
GJ1: C35.1, C36.2, C37.2, Q53.1 (G), R34.1
GND: C1.2, C2.2, C3.2, C5.2, C6.2, C7.2, C8.2, C9.2, C10.2, C11.2, D1.3 (common), D4.3 (common), D5.2 (A2), D6.2 (A2), J1.A1 (GND), J1.B1 (GND), J1.S1 (SHIELD), J4.A1 (GND), J4.B1 (GND), J4.S1 (SHIELD), R1.2, R2.2, R3.2, R4.2, R8.2, R13.2, R19.2, R34.2, TP7.1, U2.1 (GND), U3.3 (A), U4.3 (A), U5.2 (-Vin), U5.4 (-Vout); also elsewhere on the board
INJ_REF: R12.2, R13.1, U4.1 (REF)
TH_LO: R18.2, R19.1
TH_REF: C11.1, R17.2, R18.1; also elsewhere on the board
USB_UP_N: J1.A7 (DN1), J1.B7 (DN2); also elsewhere on the board
USB_UP_P: J1.A6 (DP1), J1.B6 (DP2); also elsewhere on the board
V3V3: C3.1, FB1.1, R14.1, TP5.1, U2.2 (VO); also elsewhere on the board
V5A: C10.1, R16.2, TP2.1; also elsewhere on the board
V5L: C2.1, C5.1, C35.2, Q53.3 (D), R16.1, TP1.1, U2.3 (VI), U5.1 (+Vin); also elsewhere on the board
V12: C6.1, R10.1, U5.6 (+Vout)
V12F: C7.1, C8.1, R10.2, R11.1, TP3.1; also elsewhere on the board
VBUS_IN: C1.1, D6.1 (A1), F1.2, R7.1, TP8.1; also elsewhere on the board
VBUS_J1: C36.1, C37.1, D5.1 (A1), J1.A4 (VBUS), J1.B4 (VBUS), Q53.2 (S), TP14.1
VBUS_J4: F1.1, J4.A4 (VBUS), J4.B4 (VBUS)
VDDA: C9.1, FB1.2, R17.1, TP6.1; also elsewhere on the board
VREF_CHK: R14.2, R15.1, U3.1 (REF), U3.2 (K)
V_INJ: R11.2, R12.1, TP4.1, U4.2 (K); also elsewhere on the board
V_J4: R7.2, R8.1, R9.1, TP9.1

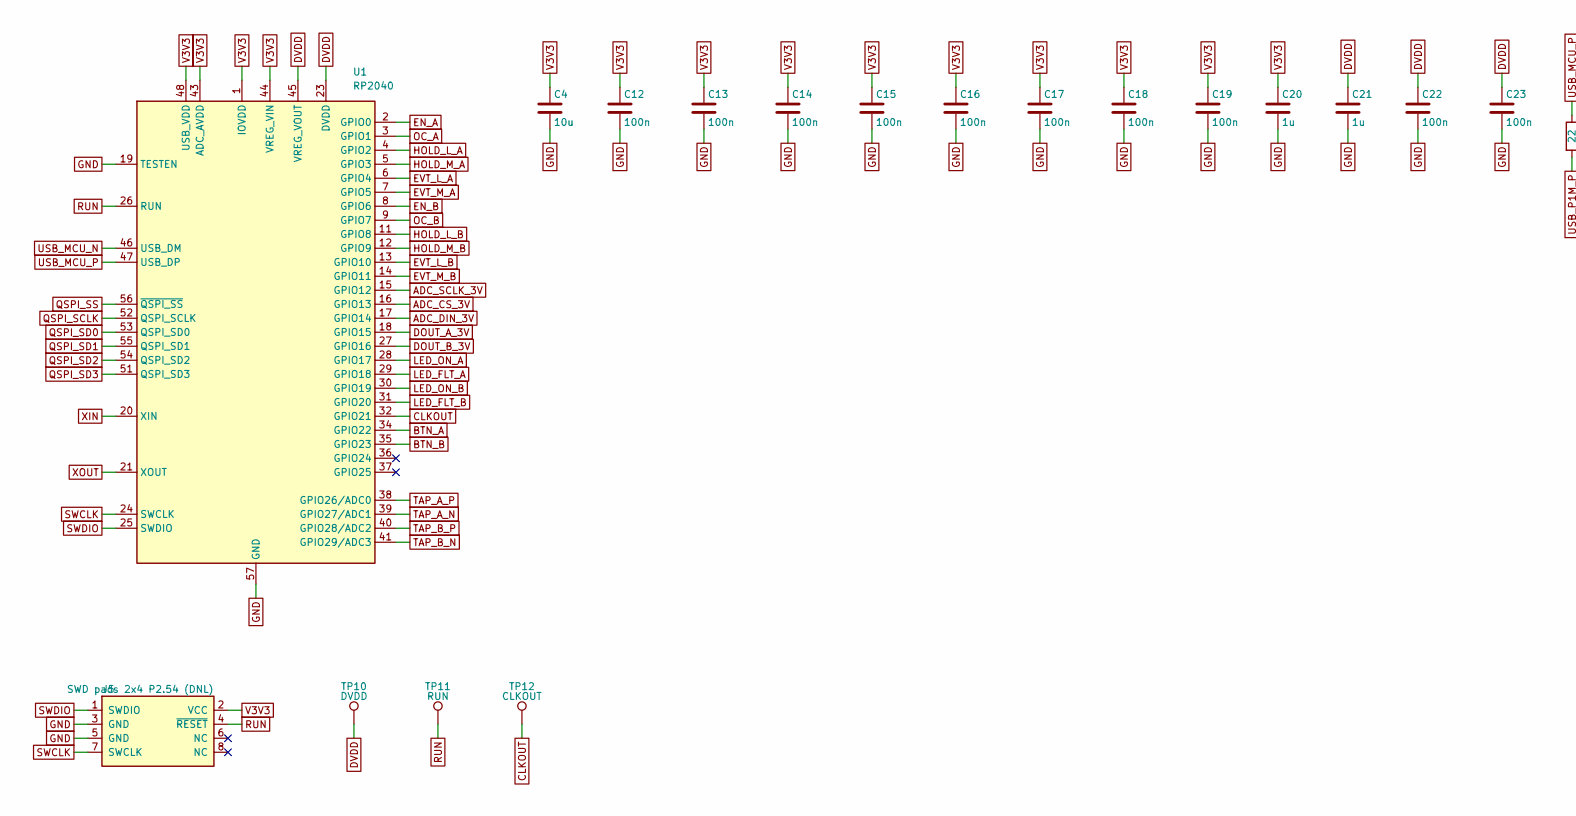
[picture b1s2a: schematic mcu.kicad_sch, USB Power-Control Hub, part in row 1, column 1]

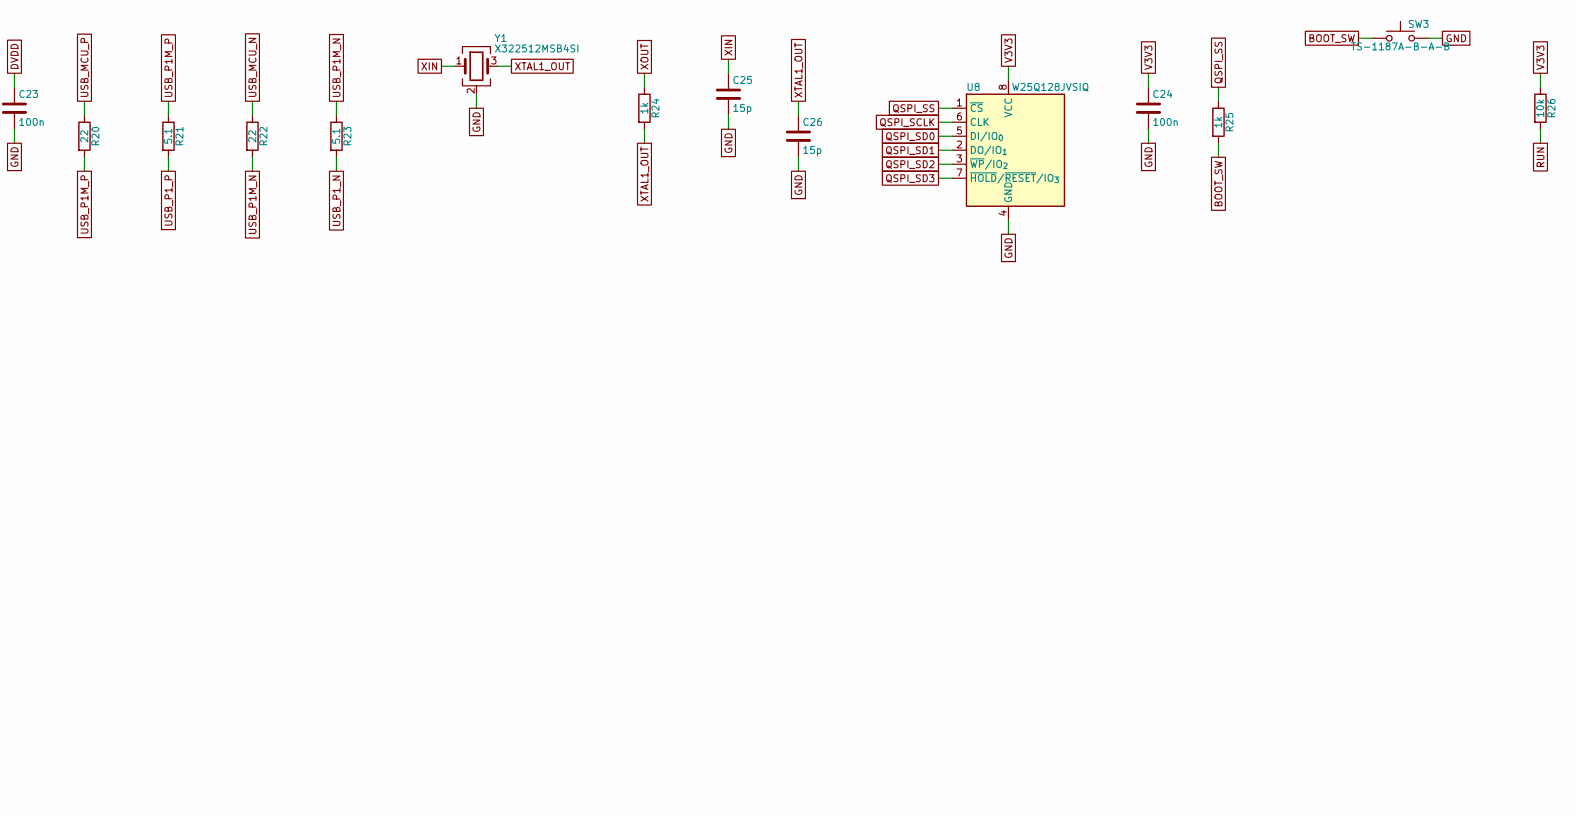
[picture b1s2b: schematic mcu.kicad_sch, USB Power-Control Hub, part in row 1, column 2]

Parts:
C4: 10u; C_0805_2012Metric; MPN CL21A106KAYNNNE; LCSC C15850
C12, C13, C14, C15, C16, C17, C18, C19, C22, C23, C24: 100n; C_0402_1005Metric; MPN CL05B104KB54PNC; LCSC C307331
C20, C21: 1u; C_0402_1005Metric; MPN CL05A105KA5NQNC; LCSC C52923
C25, C26: 15p; C_0402_1005Metric; MPN 0402CG150J500NT; LCSC C1548
J5: SWD pads 2x4 P2.54 (DNL); SWD_Pads_2x04_P2.54mm_D1.7mm_Clamp
R20, R22: 22; R_0402_1005Metric; MPN 0402WGF220JTCE; LCSC C25092
R21, R23: 5.1; R_0603_1608Metric; MPN 0603WAF510KT5E; LCSC C25197
R24, R25: 1k; R_0402_1005Metric; MPN 0402WGF1001TCE; LCSC C11702
R26: 10k; R_0402_1005Metric; MPN 0402WGF1002TCE; LCSC C25744
SW3: TS-1187A-B-A-B; SW_Push_1P1T_XKB_TS-1187A; MPN TS-1187A-B-A-B; LCSC C318884
TP10: DVDD; TestPoint_Pad_D1.0mm
TP11: RUN; TestPoint_Pad_D1.0mm
TP12: CLKOUT; TestPoint_Pad_D1.0mm
U1: RP2040; RP2040_QFN-56-1EP_7x7mm_P0.4mm_EP3.2x3.2mm; MPN RP2040; LCSC C2040
U8: W25Q128JVSIQ; SOIC-8_5.3x5.3mm_P1.27mm; MPN W25Q128JVSIQ; LCSC C97521
Y1: X322512MSB4SI; Crystal_SMD_3225-4Pin_3.2x2.5mm; MPN X322512MSB4SI; LCSC C9002

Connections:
ADC_CS_3V: U1.16 (GPIO13); also elsewhere on the board
ADC_DIN_3V: U1.17 (GPIO14); also elsewhere on the board
ADC_SCLK_3V: U1.15 (GPIO12); also elsewhere on the board
BOOT_SW: R25.2, SW3.1
BTN_A: U1.34 (GPIO22); also elsewhere on the board
BTN_B: U1.35 (GPIO23); also elsewhere on the board
CLKOUT: TP12.1, U1.32 (GPIO21)
DOUT_A_3V: U1.18 (GPIO15); also elsewhere on the board
DOUT_B_3V: U1.27 (GPIO16); also elsewhere on the board
DVDD: C21.1, C22.1, C23.1, TP10.1, U1.23 (DVDD), U1.45 (VREG_VOUT), U1.50 (DVDD)
EN_A: U1.2 (GPIO0); also elsewhere on the board
EN_B: U1.8 (GPIO6); also elsewhere on the board
EVT_L_A: U1.6 (GPIO4); also elsewhere on the board
EVT_L_B: U1.13 (GPIO10); also elsewhere on the board
EVT_M_A: U1.7 (GPIO5); also elsewhere on the board
EVT_M_B: U1.14 (GPIO11); also elsewhere on the board
GND: C4.2, C12.2, C13.2, C14.2, C15.2, C16.2, C17.2, C18.2, C19.2, C20.2, C21.2, C22.2, C23.2, C24.2, C25.2, C26.2, J5.3 (GND), J5.5 (GND), SW3.2, U1.19 (TESTEN), U1.57 (GND), U8.4 (GND), Y1.2 (G), Y1.4 (G); also elsewhere on the board
HOLD_L_A: U1.4 (GPIO2); also elsewhere on the board
HOLD_L_B: U1.11 (GPIO8); also elsewhere on the board
HOLD_M_A: U1.5 (GPIO3); also elsewhere on the board
HOLD_M_B: U1.12 (GPIO9); also elsewhere on the board
LED_FLT_A: U1.29 (GPIO18); also elsewhere on the board
LED_FLT_B: U1.31 (GPIO20); also elsewhere on the board
LED_ON_A: U1.28 (GPIO17); also elsewhere on the board
LED_ON_B: U1.30 (GPIO19); also elsewhere on the board
OC_A: U1.3 (GPIO1); also elsewhere on the board
OC_B: U1.9 (GPIO7); also elsewhere on the board
QSPI_SCLK: U1.52 (QSPI_SCLK), U8.6 (CLK)
QSPI_SD0: U1.53 (QSPI_SD0), U8.5 (DI/IO_{0})
QSPI_SD1: U1.55 (QSPI_SD1), U8.2 (DO/IO_{1})
QSPI_SD2: U1.54 (QSPI_SD2), U8.3 (~WP/IO_{2})
QSPI_SD3: U1.51 (QSPI_SD3), U8.7 (~HOLD/~RESET/IO_{3})
QSPI_SS: R25.1, U1.56 (~QSPI_SS), U8.1 (~CS)
RUN: J5.4 (~RESET), R26.2, TP11.1, U1.26 (RUN)
SWCLK: J5.7 (SWCLK), U1.24 (SWCLK)
SWDIO: J5.1 (SWDIO), U1.25 (SWDIO)
TAP_A_N: U1.39 (GPIO27/ADC1); also elsewhere on the board
TAP_A_P: U1.38 (GPIO26/ADC0); also elsewhere on the board
TAP_B_N: U1.41 (GPIO29/ADC3); also elsewhere on the board
TAP_B_P: U1.40 (GPIO28/ADC2); also elsewhere on the board
USB_MCU_N: R22.1, U1.46 (USB_DM)
USB_MCU_P: R20.1, U1.47 (USB_DP)
USB_P1M_N: R22.2, R23.1
USB_P1M_P: R20.2, R21.1
USB_P1_N: R23.2; also elsewhere on the board
USB_P1_P: R21.2; also elsewhere on the board
V3V3: C4.1, C12.1, C13.1, C14.1, C15.1, C16.1, C17.1, C18.1, C19.1, C20.1, C24.1, J5.2 (VCC), R26.1, U1.1 (IOVDD), U1.10 (IOVDD), U1.22 (IOVDD), U1.33 (IOVDD), U1.42 (IOVDD), U1.43 (ADC_AVDD), U1.44 (VREG_VIN), U1.48 (USB_VDD), U1.49 (IOVDD), U8.8 (VCC); also elsewhere on the board
XIN: C25.1, U1.20 (XIN), Y1.1
XOUT: R24.1, U1.21 (XOUT)
XTAL1_OUT: C26.1, R24.2, Y1.3

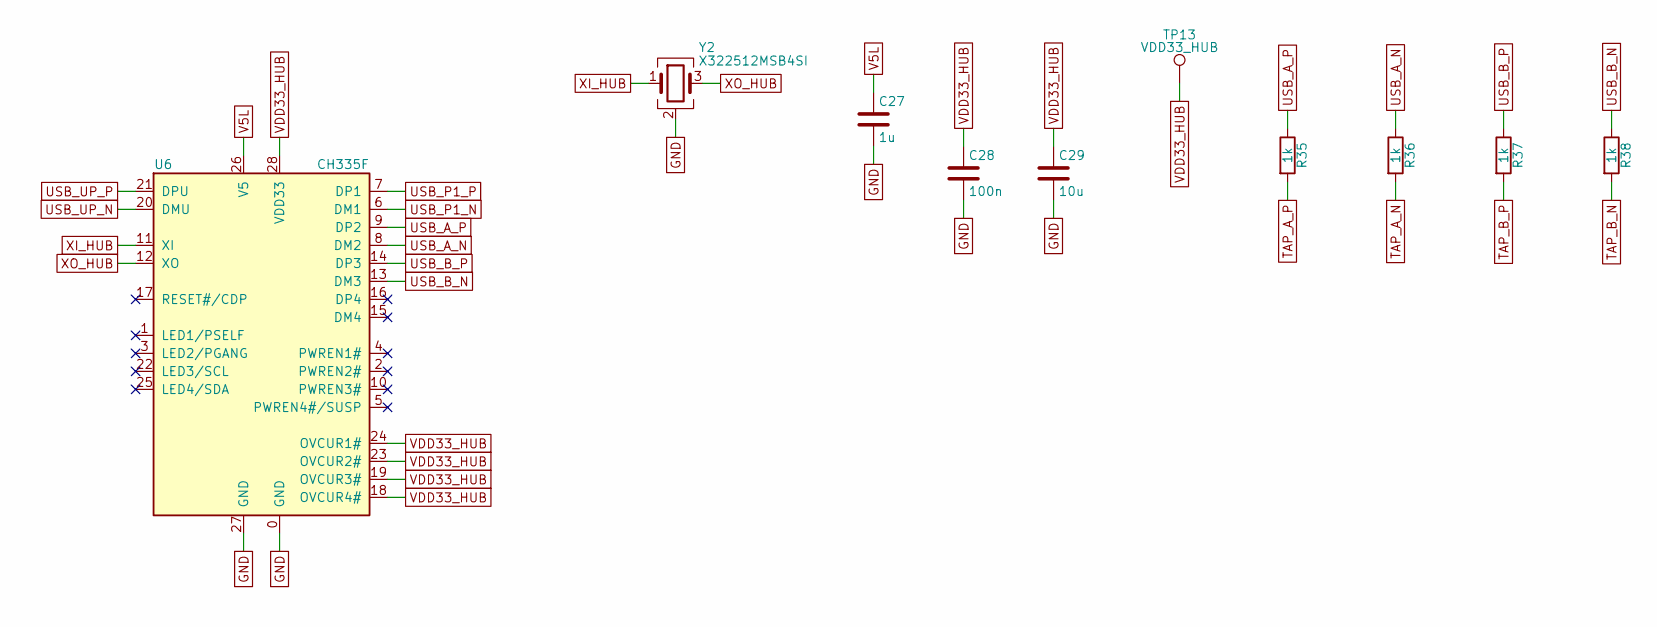
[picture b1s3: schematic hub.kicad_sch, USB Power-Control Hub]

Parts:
C27: 1u; C_0402_1005Metric; MPN CL05A105KA5NQNC; LCSC C52923
C28: 100n; C_0402_1005Metric; MPN CL05B104KB54PNC; LCSC C307331
C29: 10u; C_0805_2012Metric; MPN CL21A106KAYNNNE; LCSC C15850
R35, R36, R37, R38: 1k; R_0402_1005Metric; MPN 0402WGF1001TCE; LCSC C11702
TP13: VDD33_HUB; TestPoint_Pad_D1.0mm
U6: CH335F; CH335F_QFN-28-1EP_4x4mm_P0.4mm_EP2.7x2.7mm; MPN CH335F; LCSC C5137013
Y2: X322512MSB4SI; Crystal_SMD_3225-4Pin_3.2x2.5mm; MPN X322512MSB4SI; LCSC C9002

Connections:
GND: C27.2, C28.2, C29.2, U6.0 (GND), U6.27 (GND), Y2.2 (G), Y2.4 (G); also elsewhere on the board
TAP_A_N: R36.2; also elsewhere on the board
TAP_A_P: R35.2; also elsewhere on the board
TAP_B_N: R38.2; also elsewhere on the board
TAP_B_P: R37.2; also elsewhere on the board
USB_A_N: R36.1, U6.8 (DM2); also elsewhere on the board
USB_A_P: R35.1, U6.9 (DP2); also elsewhere on the board
USB_B_N: R38.1, U6.13 (DM3); also elsewhere on the board
USB_B_P: R37.1, U6.14 (DP3); also elsewhere on the board
USB_P1_N: U6.6 (DM1); also elsewhere on the board
USB_P1_P: U6.7 (DP1); also elsewhere on the board
USB_UP_N: U6.20 (DMU); also elsewhere on the board
USB_UP_P: U6.21 (DPU); also elsewhere on the board
V5L: C27.1, U6.26 (V5); also elsewhere on the board
VDD33_HUB: C28.1, C29.1, TP13.1, U6.18 (OVCUR4#), U6.19 (OVCUR3#), U6.23 (OVCUR2#), U6.24 (OVCUR1#), U6.28 (VDD33)
XI_HUB: U6.11 (XI), Y2.1
XO_HUB: U6.12 (XO), Y2.3

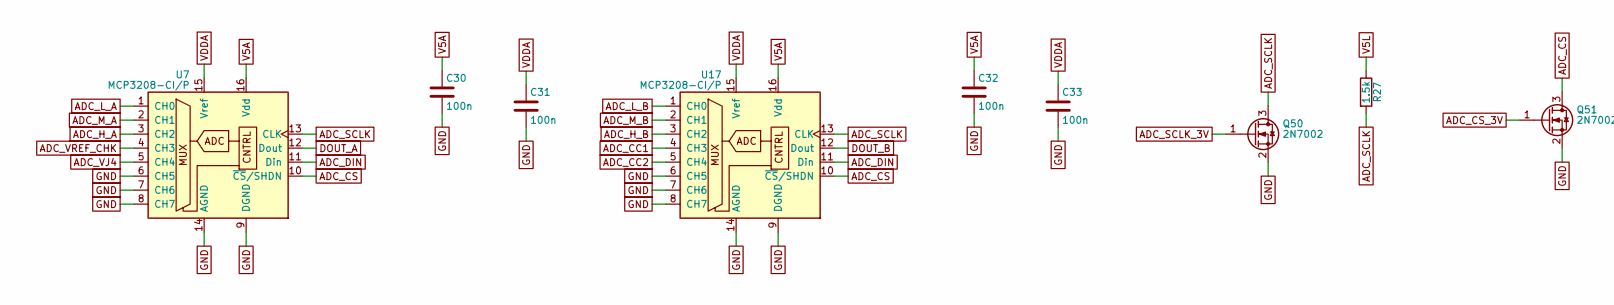
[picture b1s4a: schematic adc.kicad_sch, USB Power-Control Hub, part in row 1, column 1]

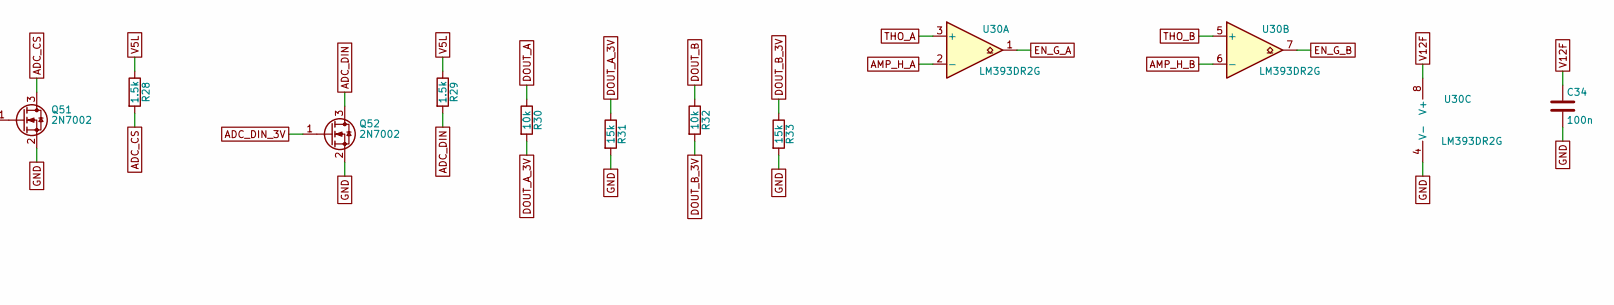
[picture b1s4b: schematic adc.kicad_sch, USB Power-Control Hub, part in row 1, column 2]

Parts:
C30, C31, C32, C33, C34: 100n; C_0402_1005Metric; MPN CL05B104KB54PNC; LCSC C307331
Q50, Q51, Q52: 2N7002; SOT-23; MPN 2N7002; LCSC C8545
R27, R28, R29: 1.5k; R_0402_1005Metric; MPN 0402WGF1501TCE; LCSC C25867
R30, R32: 10k; R_0402_1005Metric; MPN 0402WGF1002TCE; LCSC C25744
R31, R33: 15k; R_0402_1005Metric; MPN 0402WGF1502TCE; LCSC C25756
U7, U17: MCP3208-CI/P; DIP-16_W7.62mm; MPN MCP3208-CI/P
U30: LM393DR2G; SOIC-8_3.9x4.9mm_P1.27mm; MPN LM393DR2G; LCSC C7955

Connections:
ADC_CC1: U17.4 (CH3); also elsewhere on the board
ADC_CC2: U17.5 (CH4); also elsewhere on the board
ADC_CS: Q51.3 (D), R28.2, U7.10 (~CS/SHDN), U17.10 (~CS/SHDN)
ADC_CS_3V: Q51.1 (G); also elsewhere on the board
ADC_DIN: Q52.3 (D), R29.2, U7.11 (Din), U17.11 (Din)
ADC_DIN_3V: Q52.1 (G); also elsewhere on the board
ADC_H_A: U7.3 (CH2); also elsewhere on the board
ADC_H_B: U17.3 (CH2); also elsewhere on the board
ADC_L_A: U7.1 (CH0); also elsewhere on the board
ADC_L_B: U17.1 (CH0); also elsewhere on the board
ADC_M_A: U7.2 (CH1); also elsewhere on the board
ADC_M_B: U17.2 (CH1); also elsewhere on the board
ADC_SCLK: Q50.3 (D), R27.2, U7.13 (CLK), U17.13 (CLK)
ADC_SCLK_3V: Q50.1 (G); also elsewhere on the board
ADC_VJ4: U7.5 (CH4); also elsewhere on the board
ADC_VREF_CHK: U7.4 (CH3); also elsewhere on the board
AMP_H_A: U30.2 (-); also elsewhere on the board
AMP_H_B: U30.6 (-); also elsewhere on the board
DOUT_A: R30.1, U7.12 (Dout)
DOUT_A_3V: R30.2, R31.1; also elsewhere on the board
DOUT_B: R32.1, U17.12 (Dout)
DOUT_B_3V: R32.2, R33.1; also elsewhere on the board
EN_G_A: U30.1; also elsewhere on the board
EN_G_B: U30.7; also elsewhere on the board
GND: C30.2, C31.2, C32.2, C33.2, C34.2, Q50.2 (S), Q51.2 (S), Q52.2 (S), R31.2, R33.2, U7.6 (CH5), U7.7 (CH6), U7.8 (CH7), U7.9 (DGND), U7.14 (AGND), U17.6 (CH5), U17.7 (CH6), U17.8 (CH7), U17.9 (DGND), U17.14 (AGND), U30.4 (V-); also elsewhere on the board
THO_A: U30.3 (+); also elsewhere on the board
THO_B: U30.5 (+); also elsewhere on the board
V5A: C30.1, C32.1, U7.16 (Vdd), U17.16 (Vdd); also elsewhere on the board
V5L: R27.1, R28.1, R29.1; also elsewhere on the board
V12F: C34.1, U30.8 (V+); also elsewhere on the board
VDDA: C31.1, C33.1, U7.15 (Vref), U17.15 (Vref); also elsewhere on the board
